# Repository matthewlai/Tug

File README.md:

# Tug
Tensile strength testing machine.

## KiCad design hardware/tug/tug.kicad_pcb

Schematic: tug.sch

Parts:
C1, C2, C3, C4, C7: 0.1uF; C_0805
C5, C6, C9: 220uF; CP_Radial_D8.0mm_P3.50mm
C8: 0.01uF; C_0805
D1, D2: LED; LED_0805
D3: 1N4004; D_DO-15_P10.16mm_Horizontal
J1: Conn_01x04; Pin_Header_Straight_1x04_Pitch2.54mm
J2: Conn_01x04; Molex_39357_01x04
J3, J4, J5, J6, J7, J8: Conn_01x02; Pin_Header_Straight_1x02_Pitch2.54mm
J9, J10, J11: Conn_01x01; Pin_Header_Straight_1x01_Pitch2.54mm
P1: Digital; Socket_Strip_Arduino_2x18
P2: Power; Socket_Strip_Arduino_1x08
P3, P4: Analog; Socket_Strip_Arduino_1x08
P5: PWM; Socket_Strip_Arduino_1x10
P6: PWM; Socket_Strip_Arduino_1x08
P7: Communication; Socket_Strip_Arduino_1x08
P8, P9, P10, P11, P12, P13: CONN_01X01; Arduino_1pin
Q1, Q2, Q3, Q4: Q_NMOS_GDS; TO-263-3_TabPin2
R1, R2, R3, R4, R11, R12, R13: 1KR; R_0805
R5, R6, R7, R8, R9, R10: 47R; R_0805
R14: 3.5mR; R_2512
U1: MC33883; SOIC-20W_7.5x12.8mm_Pitch1.27mm
U2: INA240; SOIC-8-N

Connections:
+3V3: P2.4
+12V: C2.2, C3.1, C5.1, D3.2, J2.4, Q1.2, Q3.2, U1.1, U1.11
/0(Rx0): P6.8
/1(Tx0): P6.7
/2(**): J3.2, P6.6, U1.16
/3(**): J3.1, P6.5, R12.1, U1.17
/4(**): P6.4, R13.1, U1.20
/5(**): P6.3
/6(**): P6.2
/7(**): P6.1
/8(**): P5.10
/9(**): P5.9
/10(**): P5.8
/11(**): J4.1, P5.7, R11.1, U1.6
/12(**): J4.2, P5.6, U1.7
/13(**): P5.5
/14(Tx3): P7.1
/15(Rx3): P7.2
/16(Tx2): P7.3
/17(Rx2): P7.4
/18(Tx1): P7.5
/19(Rx1): P7.6
/20(SDA): J1.3, P7.7, R2.2
/21(SCL): J1.4, P7.8, R4.2
/22: P1.33
/23: P1.34
/24: P1.31
/25: P1.32
/26: P1.29
/27: P1.30
/28: P1.27
/29: P1.28
/30: P1.25
/31: P1.26
/32: P1.23
/33: P1.24
/34: P1.21
/35: P1.22
/36: P1.19
/37: P1.20
/38: J6.1, P1.17
/39: P1.18
/40: J7.1, P1.15
/41: P1.16
/42: J8.1, P1.13
/43: P1.14
/44: P1.11
/45: P1.12
/46: P1.9
/47: P1.10
/48: P1.7
/49: P1.8
/50(MISO): P1.5, R5.2
/51(MOSI): P1.6
/52(SCK): P1.3, R6.2
/53(SS): P1.4
/A0: J5.2, P3.1, U2.5
/A1: P3.2
/A2: P3.3
/A3: P3.4
/A4: P3.5
/A5: P3.6
/A6: P3.7
/A7: P3.8
/A8: P4.1
/A9: P4.2
/A10: P4.3
/A11: P4.4
/A12: P4.5
/A13: P4.6
/A14: P4.7
/A15: P4.8
/AREF: P5.3
/GATE_HS1: Q1.1, R7.1
/GATE_HS2: Q3.1, R9.1
/GATE_LS1: Q2.1, R8.1
/GATE_LS2: Q4.1, R10.1
/IOREF: P2.2
/M1: J2.1, R14.2, U2.1
/M2: J2.2, Q3.3, Q4.2, U1.19
/Reset: P2.3
/SCL: P5.1
/SDA: P5.2
/SRC_HS1: Q1.3, Q2.2, R14.1, U1.4, U2.8
/Vin: C6.1, D3.1, J5.1, P2.8
unnamed: C1.1, U1.10
unnamed: C2.1, U1.3
unnamed: C4.1, U1.13
unnamed: C4.2, U1.2
unnamed: D1.2, R5.1
unnamed: D2.2, R6.1
unnamed: R1.2, R2.1
unnamed: R3.2, R4.1
unnamed: R7.2, U1.5
unnamed: R8.2, U1.8
unnamed: R9.2, U1.18
unnamed: R10.2, U1.15

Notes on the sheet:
Shield for Arduino Mega Rev 3
Holes
Test Points
Gain = 50 (INA240A2)
Full range = 0.0035 * 13 * 50 = 2.275 Power dissipation = 0.0035 * 13 * 13 = 0.5915W

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
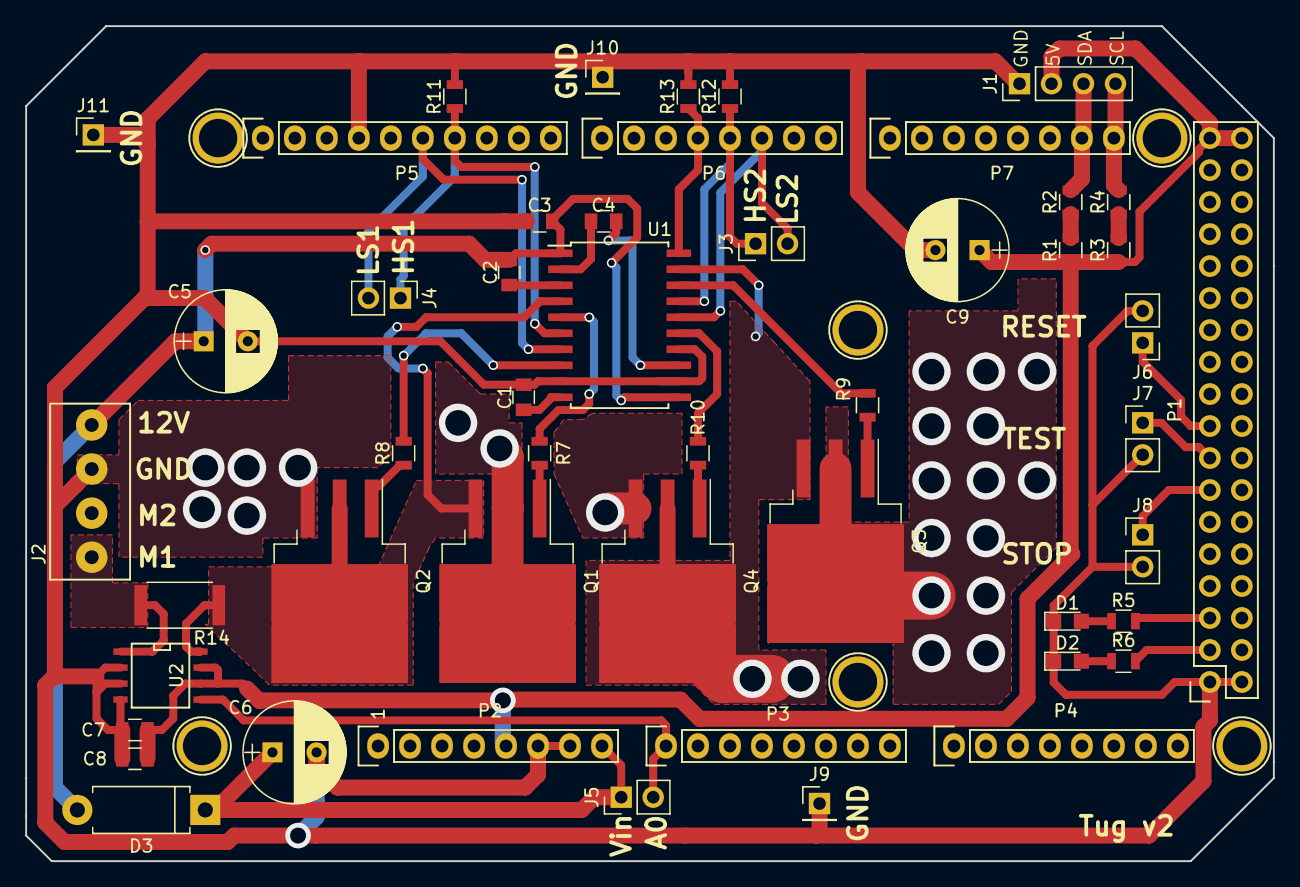
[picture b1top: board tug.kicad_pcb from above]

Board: 2 copper layers, 99.1 x 66.3 mm, 56 parts (0 on the bottom side), 36 nets.

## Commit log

2018-06-29 Added v2 PCB
2018-07-07 Switched current sensor to INA240
2021-05-16 Updated firmware
